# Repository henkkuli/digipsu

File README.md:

# Digital Power Supply
The aim of this project is to create a digitally controlled benchtop power supply.

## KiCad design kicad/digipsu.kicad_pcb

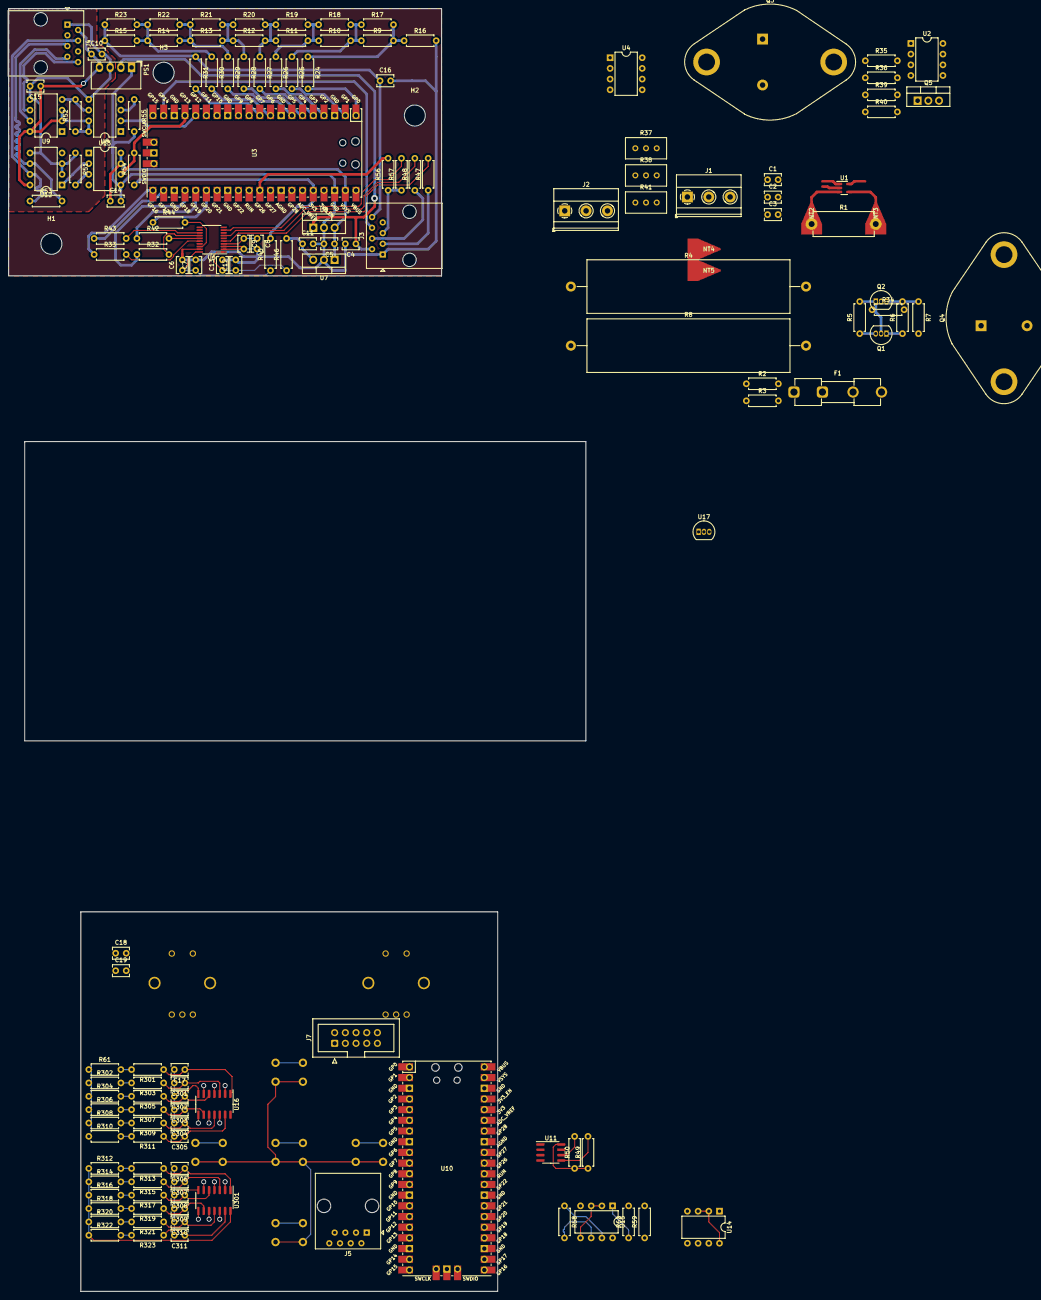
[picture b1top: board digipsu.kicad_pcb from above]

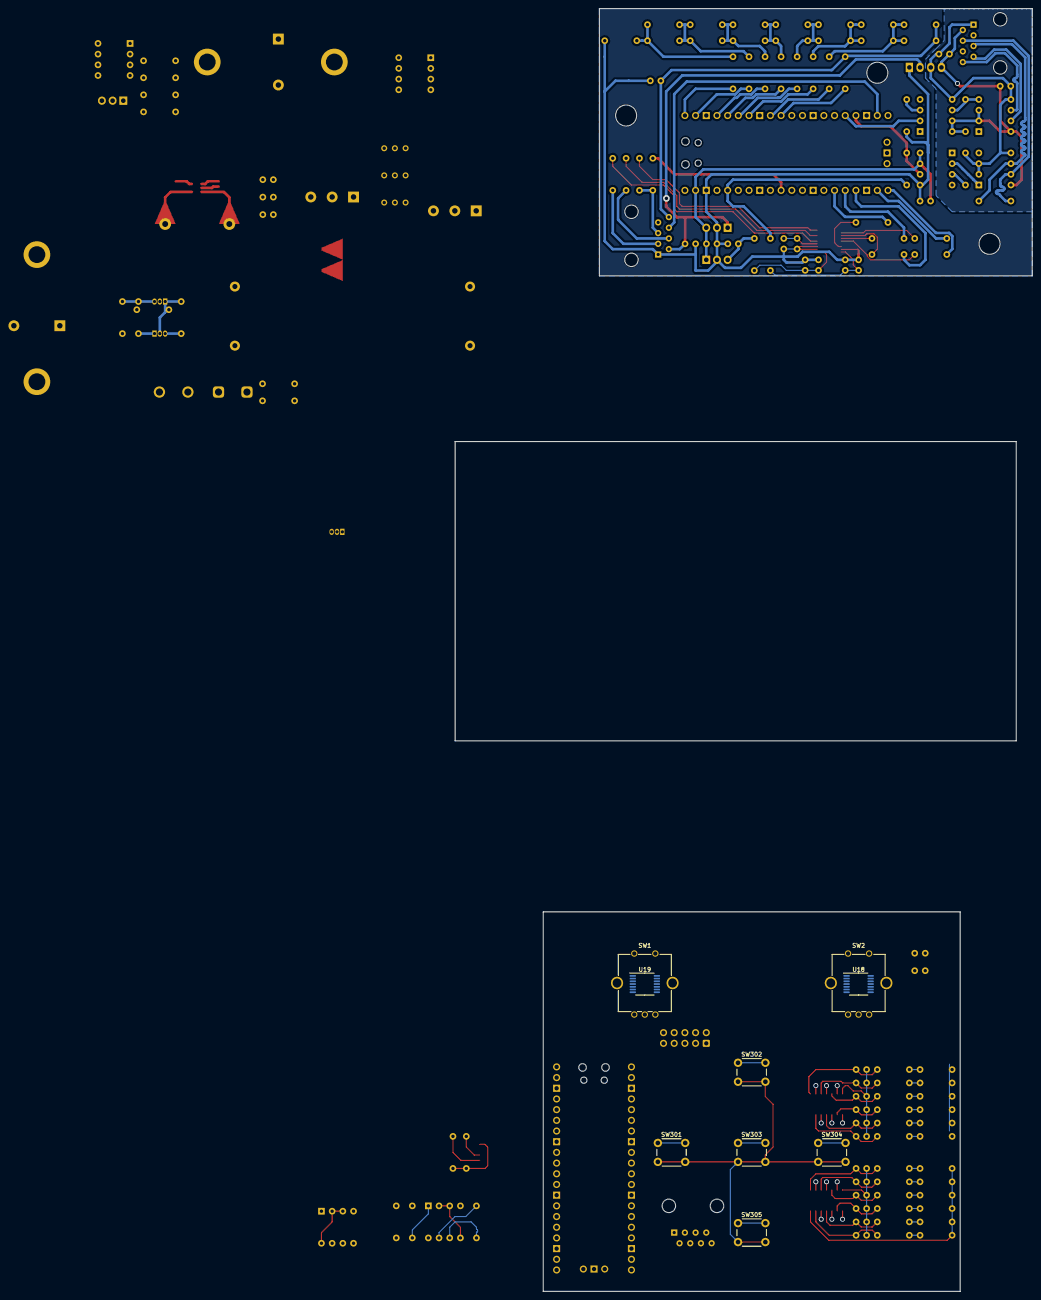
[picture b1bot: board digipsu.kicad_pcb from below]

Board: 2 copper layers, 165 parts (10 on the bottom side), 137 nets.

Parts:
B1, B2: Board
C1, C2, C3, C4, C5, C10, C11: C; C_Disc_D3.8mm_W2.6mm_P2.50mm
C6, C8, C12: 10µ; C_Disc_D3.8mm_W2.6mm_P2.50mm
C7, C9, C13, C14, C15, C17, C18, C19, C301, C302, C303, C304, C305, C306, C307, C308, C309, C310, C311: 100n; C_Disc_D3.8mm_W2.6mm_P2.50mm
C16: 10n; C_Disc_D3.8mm_W2.6mm_P2.50mm
F1: Fuse; Fuseholder_Clip-5x20mm_Eaton_1A5601-01_Inline_P20.80x6.76mm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
H1, H2, H3: MountingHole; MountingHole_5mm
J1: Screw_Terminal_01x03; TerminalBlock_Phoenix_MKDS-1,5-3-5.08_1x03_P5.08mm_Horizont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
J2: PWR IN; TerminalBlock_Phoenix_MKDS-1,5-3-5.08_1x03_P5.08mm_Horizont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
J3, J4, J5: 8P8C; RJ45_Amphenol_54602-x08_Horizontal
J7: Conn_02x05_Odd_Even; IDC-Header_2x05_P2.54mm_Vertical
NT1, NT6: NetTie_2; NetTie-2_SMD_Pad0.5mm
NT2, NT3, NT4, NT5: NetTie_2; NetTie_5mm_0.635mm
PS1: 1S4AE_1205S1.5UP; Converter_DCDC_Murata_MEE1SxxxxSC_THT
Q1: BC327; TO-92_Inline
Q2: BC337; TO-92_Inline
Q3, Q4: 2N6058; TO-3
Q5: IRLZ34N; TO-220-3_Vertical
R1: 10m; R_Axial_DIN0614_L14.3mm_D5.7mm_P15.24mm_Horizontal
R2, R7, R40, R52, R54: 1k; R_Axial_DIN0207_L6.3mm_D2.5mm_P7.62mm_Horizontal
R3, R6, R34, R35, R36, R39, R49, R50, R61, R301, R302, R303, R304, R305, R306, R307, R308, R309, R310, R311, R312, R313, R314, R315, R316, R317, R318, R319, R320, R321, R322, R323: 10k; R_Axial_DIN0207_L6.3mm_D2.5mm_P7.62mm_Horizontal
R4, R8: 100m; R_Axial_Power_L48.0mm_W12.5mm_P55.88mm
R5: 100k; R_Axial_DIN0207_L6.3mm_D2.5mm_P7.62mm_Horizontal
R9, R10, R11, R12, R13, R14, R15, R16, R17, R18, R19, R20, R21, R22, R23, R24, R25, R26, R27, R28, R29, R30, R31, R59: 2K2; R_Axial_DIN0207_L6.3mm_D2.5mm_P7.62mm_Horizontal
R32, R33, R42, R43, R44, R45, R46: 10; R_Axial_DIN0207_L6.3mm_D2.5mm_P7.62mm_Horizontal
R37, R38: 100; Potentiometer_Bourns_3296W_Vertical
R41: 200; Potentiometer_Bourns_3296W_Vertical
R47, R48, R51, R53, R55, R56, R57, R58: 100; R_Axial_DIN0207_L6.3mm_D2.5mm_P7.62mm_Horizontal
R60: 1K; R_Axial_DIN0207_L6.3mm_D2.5mm_P7.62mm_Horizontal
SW1, SW2: RotaryEncoder_Switch; RotaryEncoder_Bourns_Vertical_PEC12R-3xxxF-Sxxxx
SW301, SW302, SW303, SW304, SW305: SW_Push_45deg; SW_PUSH_6mm
U1: INA169; SOT-23-5
U2, U4: MCP6002-xP; DIP-8_W7.62mm
U3, U10: Pico; RPi_Pico_SMD_TH
U5: L7805; TO-220-3_Vertical
U6: MCP3464R; TSSOP-20_4.4x6.5mm_P0.65mm
U7: LF33_TO220; TO-220-3_Vertical
U8, U13: 6N137; DIP-8_W7.62mm
U9, U12, U14, U15: SN75176BP; DIP-8_W7.62mm
U11: M24C32-RMN; SOIC-8_3.9x4.9mm_P1.27mm
U16, U301: 74AC14; SOIC-14_3.9x8.7mm_P1.27mm
U17: DS1822; TO-92_Inline
U18, U19: AS5047D; TSSOP-14_4.4x5mm_P0.65mm

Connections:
+5V: U1.5 (V+), U2.8 (V+), U4.8 (V+)
/Controller/12V: C4.1, J3.2, PS1.2 (+Vin), U5.1 (IN)
/Controller/+3.3VA: C11.1, R46.2, U7.3 (VO)
/Controller/+3.3VD: R45.2, R54.1, U3.36 (3V3)
/Controller/+5V: C5.1, C14.1, U3.39 (VSYS), U5.3 (OUT), U7.1 (VI), U13.7 (EN), U13.8 (VCC)
/Controller/ADC_CLK: R44.1, U3.26 (GPIO20)
/Controller/Buck Voltage Sense: J3.3, R47.1
/Controller/CTRL.+5V: C10.1, C15.1, J4.2, PS1.4 (+Vout), R52.1, U8.7 (EN), U8.8 (VCC), U9.2 (~RE), U9.3 (DE), U9.8 (VCC), U12.8 (VCC)
/Controller/CTRL.GND: C10.2, C15.2, J4.1, PS1.3 (-Vout), R51.1, U8.5 (GND), U9.5 (GND), U12.2 (~RE), U12.3 (DE), U12.5 (GND)
/Controller/CTRL.RX+: J4.5, R53.2, U12.6 (A)
/Controller/CTRL.RX-: J4.4, R53.1, U12.7 (B)
/Controller/CTRL.TX+: J4.8, U9.6 (A)
/Controller/CTRL.TX-: J4.7, U9.7 (B)
/Controller/Control Voltage: C16.1, J3.8, R15.1, R23.1, R31.1
/Controller/Current Sense: J3.5, R56.1, R57.1
/Controller/DAC1: R24.2, U3.1 (GPIO0)
/Controller/DAC2: R25.2, U3.2 (GPIO1)
/Controller/DAC3: R26.2, U3.4 (GPIO2)
/Controller/DAC4: R27.2, U3.5 (GPIO3)
/Controller/DAC5: R28.2, U3.6 (GPIO4)
/Controller/DAC6: R29.2, U3.7 (GPIO5)
/Controller/DAC7: R30.2, U3.9 (GPIO6)
/Controller/DAC8: R31.2, U3.10 (GPIO7)
/Controller/GND: C4.2, C5.2, C6.2, C7.2, C11.2, C12.2, C13.2, C14.2, C16.2, J3.1, NT1.1, NT6.1, PS1.1 (-Vin), R16.2, R55.2, U3.38 (GND), U5.2 (GND), U7.2 (GND), U13.5 (GND)
/Controller/PWM-out: J3.6, U3.19 (GPIO14)
/Controller/RX: R54.2, U3.17 (GPIO13), U13.6 (VO)
/Controller/SPI.MISO: R33.1, U3.21 (GPIO16)
/Controller/SPI.MOSI: R42.1, U3.25 (GPIO19)
/Controller/SPI.SCK: R32.1, U3.24 (GPIO18)
/Controller/SPI.SS: R43.1, U3.22 (GPIO17)
/Controller/TX: U3.16 (GPIO12), U8.2 (A)
/Controller/Voltage Sense: J3.4, R48.1
/CurrentSenseX1: U2.1, U2.2 (-), U2.5 (+)
/CurrentSenseX10: R39.1, U2.7
/User Interface/+3.3V: J7.1, R49.1, R50.1, R61.1, R302.1, R304.1, R306.1, R308.1, R310.1, R312.1, R314.1, R316.1, R318.1, R320.1, R322.1, U10.36 (3V3), U11.8 (VCC), U16.14 (VCC), U301.14 (VCC)
/User Interface/+5V: J5.2, U10.39 (VSYS), U14.2 (~RE), U14.3 (DE), U14.8 (VCC), U15.8 (VCC)
/User Interface/CTRL.RX+: J5.8, R58.2, U15.6 (A)
/User Interface/CTRL.RX-: J5.7, R58.1, U15.7 (B)
/User Interface/CTRL.TX+: J5.4, U14.6 (A)
/User Interface/CTRL.TX-: J5.5, U14.7 (B)
/User Interface/ENC.CLK: U18.2 (CLK), U19.2 (CLK)
/User Interface/ENC.MISO: U18.3 (MISO), U19.3 (MISO)
/User Interface/ENC.MOSI: U18.4 (MOSI), U19.4 (MOSI)
/User Interface/GND: C17.2, C18.2, C19.2, C301.2, C302.2, C303.2, C304.2, C305.2, C306.2, C307.2, C308.2, C309.2, C310.2, C311.2, J5.1, J7.2, R59.1, SW1.C, SW1.S2, SW2.C, SW2.S2, SW301.2, SW302.2, SW303.2, SW304.2, SW305.2, U10.38 (GND), U11.1 (E0), U11.2 (E1), U11.3 (E2), U11.4 (VSS), U11.7 (~WC), U14.5 (GND), U15.2 (~RE), U15.3 (DE), U15.5 (GND), U16.7 (GND), U18.5 (TST), U18.13 (GND), U19.5 (TST), U19.13 (GND), U301.7 (GND)
/User Interface/RX: R59.2, R60.2, U10.2 (GPIO1)
/User Interface/SCL: J7.5, R50.2, U10.12 (GPIO9), U11.6 (SCL)
/User Interface/SDA: J7.6, R49.2, U10.11 (GPIO8), U11.5 (SDA)
/User Interface/SWin1: R61.2, R301.2, SW2.S1
/User Interface/SWin2: R302.2, R303.2, SW2.A
/User Interface/SWin3: R304.2, R305.2, SW2.B
/User Interface/SWin4: R306.2, R307.2, SW1.S1
/User Interface/SWin5: R308.2, R309.2, SW1.A
/User Interface/SWin6: R310.2, R311.2, SW1.B
/User Interface/SWin7: R312.2, R313.2, SW302.1
/User Interface/SWin8: R314.2, R315.2, SW301.1
/User Interface/SWin9: R316.2, R317.2, SW303.1
/User Interface/SWin10: R318.2, R319.2, SW304.1
/User Interface/SWin11: R320.2, R321.2, SW305.1
/User Interface/SWin12: R322.2, R323.2
/User Interface/SWout1: U10.4 (GPIO2), U16.2
/User Interface/SWout2: U10.5 (GPIO3), U16.4, U18.6 (B), U18.7 (A)
/User Interface/SWout3: U10.6 (GPIO4), U16.6
/User Interface/SWout4: U10.7 (GPIO5), U16.8
/User Interface/SWout5: U10.9 (GPIO6), U16.10, U19.7 (A)
/User Interface/SWout6: U10.10 (GPIO7), U16.12, U19.6 (B)
/User Interface/SWout7: U10.27 (GPIO21), U301.2
/User Interface/SWout8: U10.26 (GPIO20), U301.4
/User Interface/SWout9: U10.25 (GPIO19), U301.6
/User Interface/SWout10: U10.24 (GPIO18), U301.8
/User Interface/SWout11: U10.22 (GPIO17), U301.10
/User Interface/SWout12: U10.21 (GPIO16), U301.12
/User Interface/TX: U10.1 (GPIO0), U14.4 (D)
/VoltageSense: U4.1, U4.2 (-)
GND: R36.1, R40.2, U1.2 (GND), U2.4 (V-), U4.4 (V-)
GNDPWR: C1.2, C2.2, C3.2, J1.3, J2.1, NT5.1
unnamed: C17.1, R301.1, U16.1
unnamed: C301.1, R303.1, U16.3
unnamed: C302.1, R305.1, U16.5
unnamed: C303.1, R307.1, U16.9
unnamed: C304.1, R309.1, U16.11
unnamed: C305.1, R311.1, U16.13
unnamed: C306.1, R313.1, U301.1
unnamed: C307.1, R315.1, U301.3
unnamed: C308.1, R317.1, U301.5
unnamed: C309.1, R319.1, U301.9
unnamed: C310.1, R321.1, U301.11
unnamed: C311.1, R323.1, U301.13
unnamed: J1.1, NT3.1, NT4.1, R1.2
unnamed: F1.2, J2.3
unnamed: NT4.2, R3.1
unnamed: NT5.2, R2.2
unnamed: Q1.2 (B), Q2.1 (C), R5.2
unnamed: Q1.1 (C), Q3.1 (B), Q4.1 (B), R6.1
unnamed: Q2.3 (E), R6.2, R7.1
unnamed: Q3.3 (C), R4.2
unnamed: C1.1, NT2.1, Q3.2 (E), Q4.2 (E), R1.1
unnamed: Q4.3 (C), R8.2
unnamed: R2.1, R38.1
unnamed: R10.1, R11.2, R18.1, R19.2, R26.1
unnamed: R9.1, R10.2, R17.1, R18.2, R25.1
unnamed: R11.1, R12.2, R19.1, R20.2, R27.1
unnamed: R12.1, R13.2, R20.1, R21.2, R28.1
unnamed: R13.1, R14.2, R21.1, R22.2, R29.1
unnamed: R14.1, R15.2, R22.1, R23.2, R30.1
unnamed: R9.2, R16.1, R17.2, R24.1
unnamed: R34.1, R35.1
unnamed: R35.2, R37.2
unnamed: R36.2, R37.1
unnamed: R40.1, R41.1
unnamed: NT2.2, U1.3 (+)
unnamed: NT3.2, U1.4 (-)
unnamed: R34.2, U1.1, U2.3 (+)
unnamed: R39.2, R41.2, U2.6 (-)
unnamed: R56.2, U3.31 (GPIO26_ADC0)
unnamed: R3.2, R38.2, U4.3 (+)
unnamed: C2.1, R4.1, R8.1, U4.5 (+)
unnamed: C8.2, C9.2, NT6.2, U6.2 (AGND), U6.3 (REFIN-)
unnamed: C12.1, C13.1, R46.1, U6.1 (AVdd)
unnamed: R47.2, U6.5 (CH0)
unnamed: R48.2, U6.7 (CH2)
unnamed: R57.2, U6.9 (CH4)
unnamed: NT1.2, U6.19 (DGND)
unnamed: C6.1, C7.1, R45.1, U6.20 (DVdd)
unnamed: R44.2, U6.18 (MCLK)
unnamed: C8.1, C9.1, U6.4 (REFIN+/OUT)
unnamed: R32.2, U6.14 (SCK)
unnamed: R42.2, U6.15 (SDI)
unnamed: R33.2, U6.16 (SDO)
unnamed: R43.2, U6.13 (~CS)
unnamed: R55.1, U8.3 (C)
unnamed: R52.2, U8.6 (VO), U9.4 (D)
unnamed: U12.1 (R), U13.2 (A)
unnamed: R51.2, U13.3 (C)
unnamed: R60.1, U15.1 (R)
unnamed: C18.1, U18.11 (VDD), U18.12 (VDD3V3)
unnamed: C19.1, U19.11 (VDD), U19.12 (VDD3V3)
VBUS: C3.1, F1.1, Q1.3 (E), Q5.2 (D), R5.1

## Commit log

2023-06-10 Add KiBot for test
2023-06-10 Small change for KiBot testing
2023-06-10 Use YES instead of true
2023-06-10 Allow running KiBot manually
2023-06-10 Upload the whole repo as an artifact
2023-08-18 Update design
2023-09-04 Complete controller board
2023-09-08 Add kibot config
2023-09-08 Specify kicad files
2023-09-08 Comment out failing kibot outputs
2023-09-08 Restrict files to upload
2023-09-08 Prune most of unnecessary kibot outputs
2023-09-08 Separate boards automatically
2023-09-11 Add missing updates on config.kibot.yaml
2023-09-11 Add latest changes to fix CI
2023-09-13 Compile gerber and drill files in one zip
2023-09-20 Start UI pcb design
2023-09-20 Start CAD modeling for case
2023-09-20 Add very short intro to README
2023-10-01 Continue on UI board design
